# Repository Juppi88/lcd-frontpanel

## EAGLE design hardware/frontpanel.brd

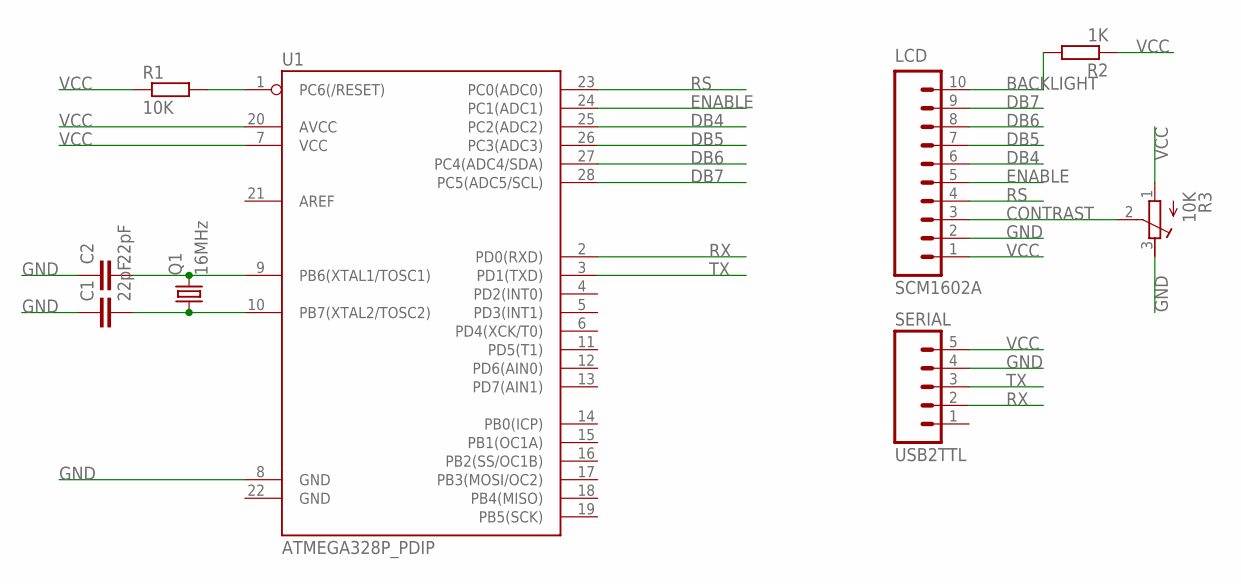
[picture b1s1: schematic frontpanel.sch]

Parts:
C1, C2: 22pF; CAP-PTH-SMALL-KIT
LCD: SCM1602A; 1X10
Q1: 16MHz; HC49/S
R1: 10K; 0204/7
R2: 1K; 0204/7
R3: 10K; RTRIM64X
SERIAL: USB2TTL; 1X05
U1: ATMEGA328P_PDIP; DIL28-3

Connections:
BACKLIGHT: LCD.10, R2.2
CONTRAST: LCD.3, R3.2 (S)
DB4: LCD.6, U1.25 (PC2(ADC2))
DB5: LCD.7, U1.26 (PC3(ADC3))
DB6: LCD.8, U1.27 (PC4(ADC4/SDA))
DB7: LCD.9, U1.28 (PC5(ADC5/SCL))
ENABLE: LCD.5, U1.24 (PC1(ADC1))
GND: C1.1, C2.1, LCD.2, R3.3 (E), SERIAL.4, U1.8 (GND)
unnamed: R1.2, U1.1 (PC6(/RESET))
unnamed: C1.2, Q1.1, U1.10 (PB7(XTAL2/TOSC2))
unnamed: C2.2, Q1.2, U1.9 (PB6(XTAL1/TOSC1))
RS: LCD.4, U1.23 (PC0(ADC0))
RX: SERIAL.2, U1.2 (PD0(RXD))
TX: SERIAL.3, U1.3 (PD1(TXD))
VCC: LCD.1, R1.1, R2.1, R3.1 (A), SERIAL.5, U1.7 (VCC), U1.20 (AVCC)

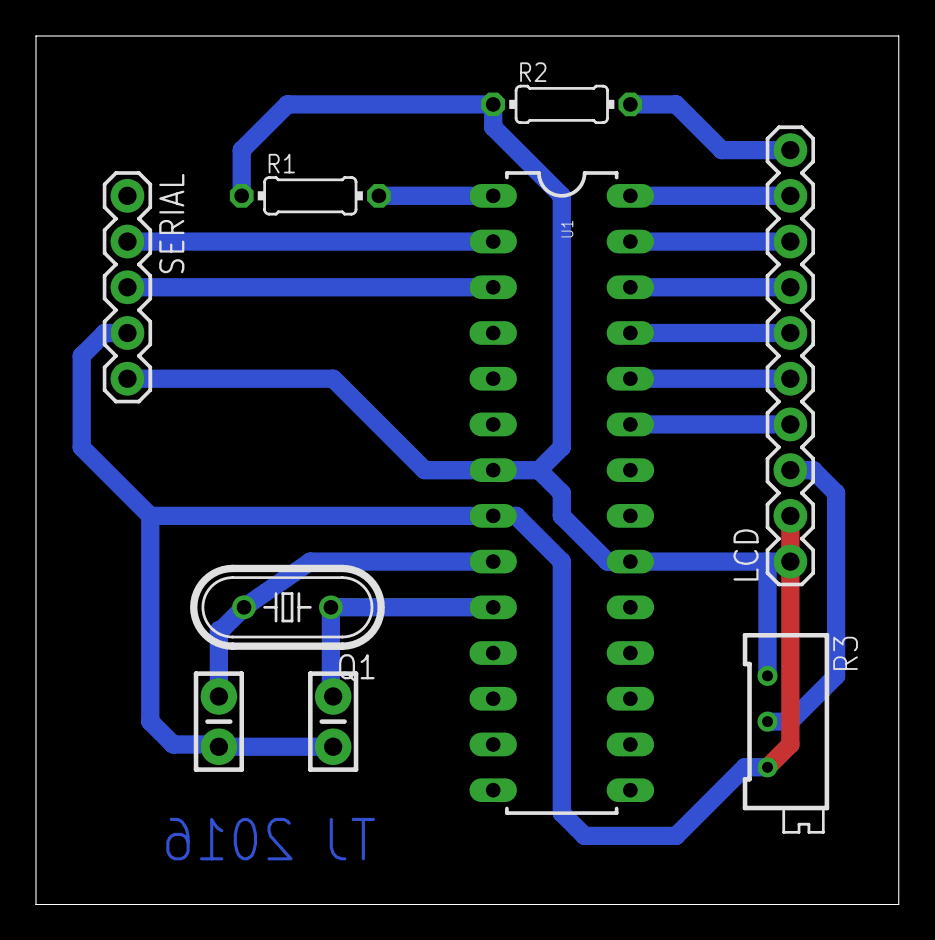
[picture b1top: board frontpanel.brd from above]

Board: 2 copper layers, 47.9 x 48.2 mm, 9 parts (0 on the bottom side), 15 nets.

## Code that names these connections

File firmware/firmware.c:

#include <avr/io.h>
#include <stdio.h>
#include "avr-lcd1602/lcd1602.h"
#include "avr-serial/serial.h"
#include "protocol.h"

static struct lcd_t lcd;

static void initialize()
{
	// Create an interface to the display and initialize it.
	lcd = lcd_initialize(PC0, PC1, PC2, PC3, PC4, PC5);

	// Create some custom characters just for fun.
	uint8_t glyph1[] = { 0x00, 0x10, 0x08, 0x04, 0x02, 0x01, 0x00, 0x00 }; // Backslash
	uint8_t glyph2[] = { 0x00, 0x0A, 0x0A, 0x0A, 0x00, 0x11, 0x0E, 0x00 }; // Smiley face
	uint8_t glyph3[] = { 0x00, 0x0A, 0x0A, 0x0A, 0x00, 0x0E, 0x11, 0x00 }; // Sad face

	lcd_create_glyph(&lcd, 0, glyph1);
	lcd_create_glyph(&lcd, 1, glyph2);
	lcd_create_glyph(&lcd, 2, glyph3);

	// Initialize the serial connection.
	serial_initialize();

	// Print some initial text which is displayed on startup.
	lcd_print_glyph(&lcd, ' ');
	lcd_print_glyph(&lcd, 0x00);
	lcd_print_glyph(&lcd, 0x00);
	lcd_print(&lcd, "BUILDSERVER");
}

static void set_cursor(void)
{
	struct packet_set_cursor_t p;
	serial_read_data(&p, sizeof(p));

	lcd_set_cursor(&lcd, p.row, p.column);
}

static void print(void)
{
	char buffer[MAX_TEXT_LEN + 1];

	// Get the length of the message.
	uint8_t len = (uint8_t)serial_read();

	// Make sure the data fits into the buffer.
	if (len > MAX_TEXT_LEN) {
		len = MAX_TEXT_LEN;
	}

	// Read the actual message and null terminate it.
	serial_read_data(buffer, len);
	buffer[len] = 0;

	// Print it.
	lcd_print(&lcd, buffer);
}

static void print_glyph(void)
{
	struct packet_print_glyph_t p;
	serial_read_data(&p, sizeof(p));

	lcd_print_glyph(&lcd, p.index);
}

static void create_glyph(void)
{
	struct packet_create_glyph_t p;
	serial_read_data(&p, sizeof(p));

	lcd_create_glyph(&lcd, p.index, p.glyph);
}

int main(void)
{
	char errmsg[32];

	initialize();

	for (;;) {

		if (serial_is_data_available()) {

			char packet = serial_read();

			switch (packet) {

			case PACKET_CLEAR:
				lcd_clear(&lcd);
				break;

			case PACKET_SET_CURSOR:
				set_cursor();
				break;

			case PACKET_PRINT:
				print();
				break;

			case PACKET_PRINT_GLYPH:
				print_glyph();
				break;

			case PACKET_CREATE_GLYPH:
				create_glyph();
				break;

			case 0:
				break;

			default:
				sprintf(errmsg, "READ ERROR: %d", packet);

				lcd_clear(&lcd);
				lcd_print(&lcd, errmsg);

				break;
			}
		}
	}

	return 0;
}

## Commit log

2016-08-15 Initial commit.
2016-08-15 Add schematics.
2016-08-15 Add Windows client project.
2018-01-08 Update submodule repositories.

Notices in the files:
parts and their libraries:
SparkFun-Capacitors: Licensing: Creative Commons ShareAlike 4.0 International - https://creativecommons.org/licenses/by-sa/4.0
